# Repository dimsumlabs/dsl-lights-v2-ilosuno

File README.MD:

# dsl-light v2 (ilo suno)

This repo contains the electronic design files of the new revision of DSL's RGBW LED driver board.

The original one was designed by lionello. Since I don't have Eagle, I'm redrawing the whole thing. I made the following enhancements:

* Added white LED channel
* Using ESP-WROOM-02 instead of ESP12. Both are ESP8266-based chip.
* Added bypass capacitors
* Added reverse polarity protection for voltage regulator input
* Using SMD components except for connectors
* Added mounting holes
* Replaced LDO with DC-DC buck converter
* Added power indicator
* Added programming header and removed unneeded programming button
* Added GPIO header for potential future expansion
* Replaced first-stage BJT with MOSFET
* Added gate resistor to MOSFET
* Added Dimsumlabs' logo and other info on silk mark

This new hardware design is backward-compatible with the original firmware.

## Installation Progress in DSL

2024-08-14:

2024-10-29:

2025-09-13:

* Programmed the driver board with correct SSID and password so that it can be integrated with the lighting-related feature in DSL
* Obtained MAC and IP address of the driver boards so that the helios DNS can be fixed. The fix is to be performed by trouble
* Performed material recon for the installation of the backside

Thanks Nigel for wiring up the frontside driver board to the switch board. Also thanks Nigel for offering to help installing the LED strips to the backside.

2025-09-14:

* trouble had updated the DNS record. Now that the driver boards' web interface can be accessed via a domain name

2025-09-27:

* As Nigel's doing renovation, plan changed. The orignally installed strips had been rotated. Instead of using 2 LED controllers, we gotta use 5 of them. Sadale had put the 5 strips up but only one of them has controller installed for now.

2025-10-18:

* Ordered 10pcs additional units

2025-10-19:

* Drawn enclosure for the device

2025-11-01:

* Revised enclosure design with vents added
* Performed programming, flashing and testing on the 10pcs batch

2025-12-31:

* I haven't logged the progress but based on my visit in the past weeks, the installation has been completed (5 sets of LED controllers hanging on the ceiling). strerror had also vibe coded a web interface for controlling the lights!

## Credit

* lionello - For making the original design and the firmware
* Sadale - For revising the hardware design and doing the installation
* nigel - for reviewing the hardware design and doing the installation
* trouble - for proposing starting this project and reviewing the hardware design
* strerror - for doing the installation and making the web interface
* Other DSL members - for getting the whole thing installed to DSL, maintaining the firmware, etc.

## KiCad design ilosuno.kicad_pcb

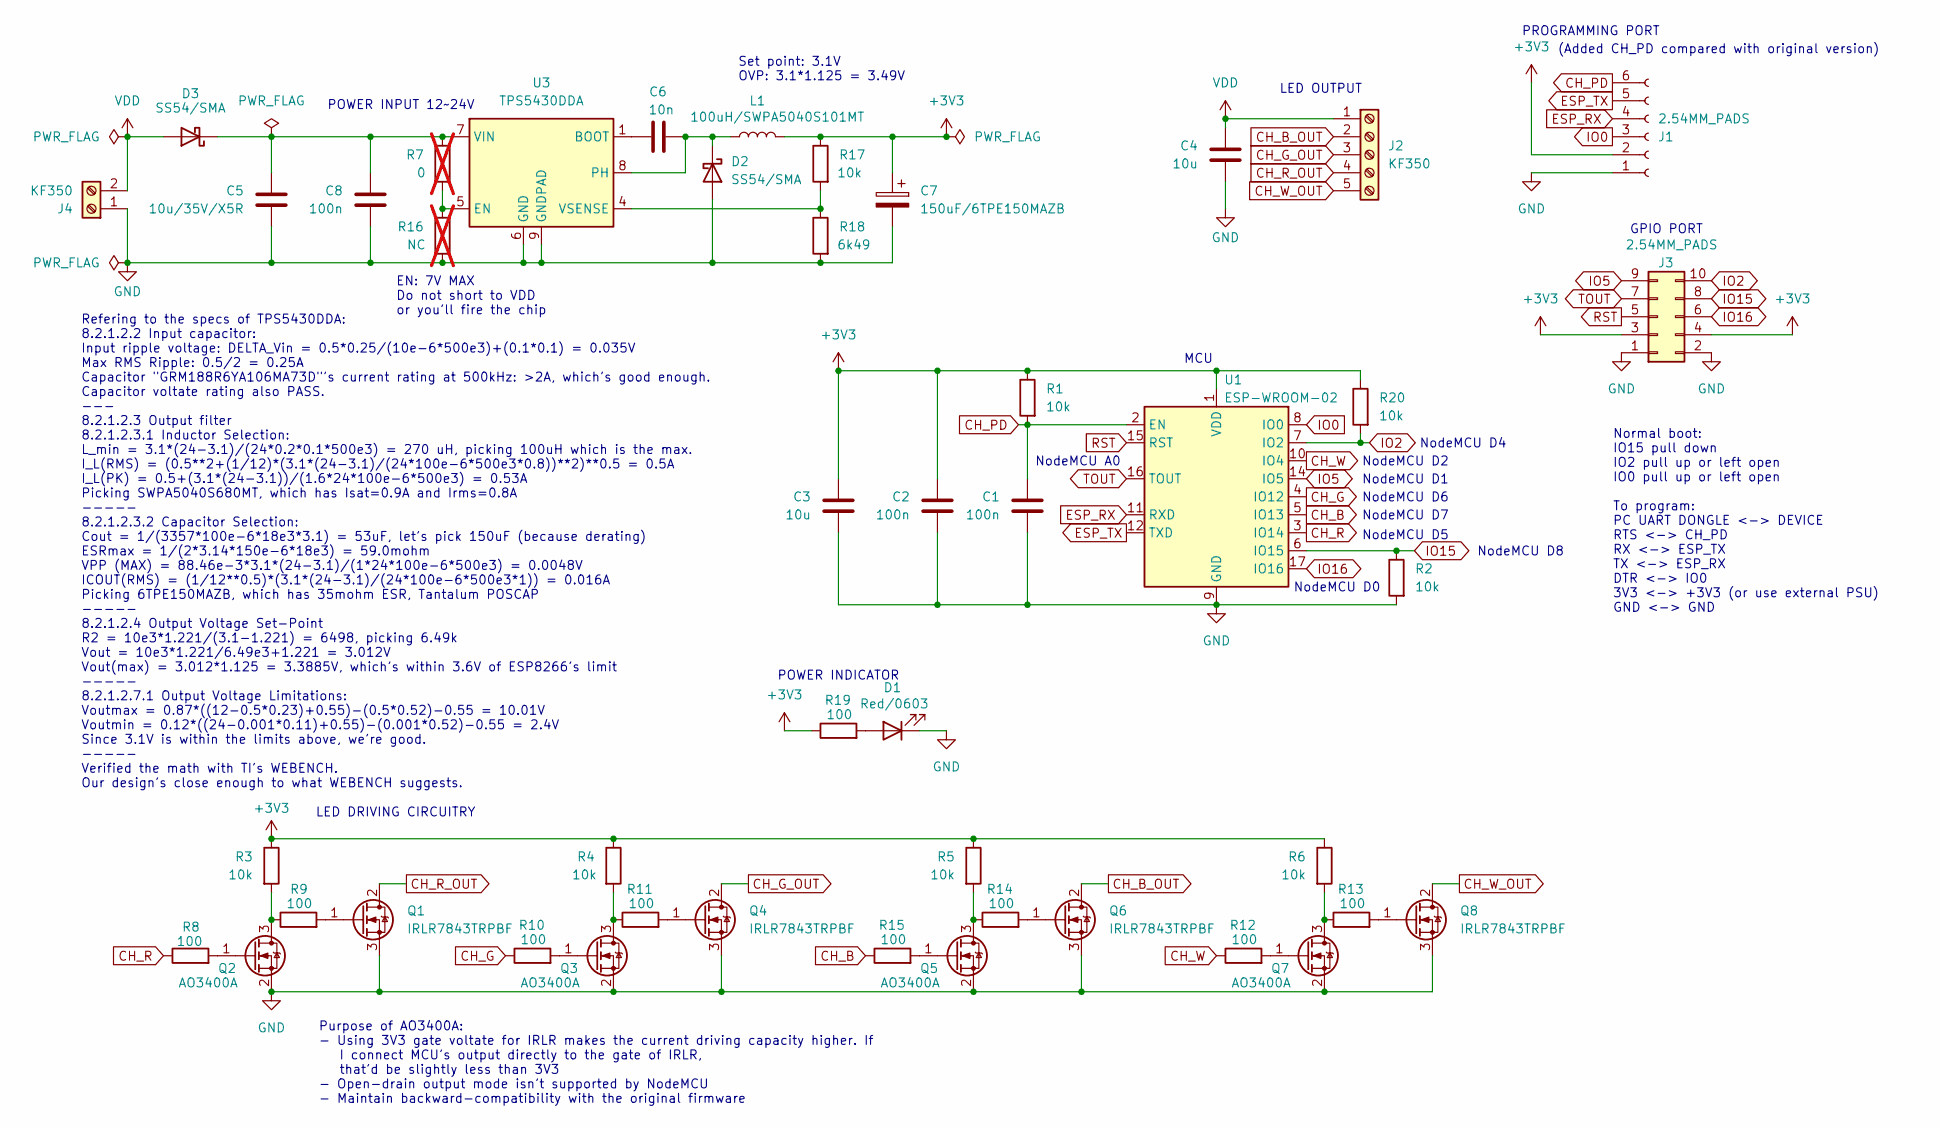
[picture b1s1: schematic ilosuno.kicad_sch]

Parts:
C1, C2, C8: 100n; C_0603_1608Metric; LCSC C14663
C3, C4: 10u; C_0805_2012Metric; LCSC C162422
C5: 10u/35V/X5R; C_0805_2012Metric; LCSC C162422
C6: 10n; C_0603_1608Metric; LCSC C57112
C7: 150uF/6TPE150MAZB; CP_EIA-3528-21_Kemet-B; LCSC C79110
D1: Red/0603; LED_0603_1608Metric; JLC Basic Part Y
D2, D3: SS54/SMA; D_SMA; LCSC C22452
J1: 2.54MM_PADS; PinHeader_1x06_P2.54mm_Vertical
J2: KF350; TerminalBlock_4Ucon_1x05_P3.50mm_Horizontal; LCSC both:C474893,C474892
J3: 2.54MM_PADS; PinHeader_2x05_P2.54mm_Vertical
J4: KF350; TerminalBlock_4Ucon_1x02_P3.50mm_Horizontal; LCSC C474892
L1: 100uH/SWPA5040S101MT; L_Sunlord_SWPA5040S; LCSC C88132
Q1, Q4, Q6, Q8: IRLR7843TRPBF; TO-252-2-with-heatsink; LCSC C21988
Q2, Q3, Q5, Q7: AO3400A; SOT-23; LCSC C20917
R1, R2, R3, R4, R5, R6, R17, R20: 10k; R_0603_1608Metric; LCSC C25804
R7: 0; R_0603_1608Metric; LCSC C21189; not fitted
R8, R9, R10, R11, R12, R13, R14, R15, R19: 100; R_0603_1608Metric; LCSC C22775
R16: NC; R_0603_1608Metric; not fitted
R18: 6k49; R_0603_1608Metric; LCSC C23088
U1: ESP-WROOM-02; LCSC C529584
U3: TPS5430DDA; TI_SO-PowerPAD-8_ThermalVias; LCSC C9864

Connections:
+3V3: C2.1, C3.1, C7.1, J1.2, J3.3, J3.4, L1.2, R1.1, R3.1, R4.1, R5.1, R6.1, R17.1, R19.1, R20.1, U1.1 (VDD)
CH_B: R15.1, U1.5 (IO13)
CH_B_OUT: J2.2, Q6.2 (D)
CH_G: R10.1, U1.4 (IO12)
CH_G_OUT: J2.3, Q4.2 (D)
CH_PD: C1.1, J1.6, R1.2, U1.2 (EN)
CH_R: R8.1, U1.3 (IO14)
CH_R_OUT: J2.4, Q1.2 (D)
CH_W: R12.1, U1.10 (IO4)
CH_W_OUT: J2.5, Q8.2 (D)
ESP_RX: J1.4, U1.11 (RXD)
ESP_TX: J1.5, U1.12 (TXD)
GND: C1.2, C2.2, C3.2, C4.2, C5.2, C7.2, C8.2, D1.1 (K), D2.2 (A), J1.1, J3.1, J3.2, J4.1, Q1.3 (S), Q2.2 (S), Q3.2 (S), Q4.3 (S), Q5.2 (S), Q6.3 (S), Q7.2 (S), Q8.3 (S), R2.2, R16.2, R18.2, U1.9 (GND), U1.13 (GND), U1.18 (GND), U1.19 (GND), U3.6 (GND), U3.9 (GNDPAD)
IO0: J1.3, U1.8 (IO0)
IO2: J3.10, R20.2, U1.7 (IO2)
IO5: J3.9, U1.14 (IO5)
IO15: J3.8, R2.1, U1.6 (IO15)
IO16: J3.6, U1.17 (IO16)
unnamed: D1.2 (A), R19.2
unnamed: C6.1, D2.1 (K), L1.1, U3.8 (PH)
unnamed: C5.1, C8.1, D3.1 (K), R7.1, U3.7 (VIN)
unnamed: Q1.1 (G), R9.2
unnamed: Q2.3 (D), R3.2, R9.1
unnamed: Q2.1 (G), R8.2
unnamed: Q3.3 (D), R4.2, R11.1
unnamed: Q3.1 (G), R10.2
unnamed: Q4.1 (G), R11.2
unnamed: Q5.3 (D), R5.2, R14.1
unnamed: Q5.1 (G), R15.2
unnamed: Q6.1 (G), R14.2
unnamed: Q7.3 (D), R6.2, R13.1
unnamed: Q7.1 (G), R12.2
unnamed: Q8.1 (G), R13.2
unnamed: C6.2, U3.1 (BOOT)
unnamed: R7.2, R16.1, U3.5 (EN)
unnamed: R17.2, R18.1, U3.4 (VSENSE)
RST: J3.5, U1.15 (RST)
TOUT: J3.7, U1.16 (TOUT)
VDD: C4.1, D3.2 (A), J2.1, J4.2

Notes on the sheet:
LED DRIVING CIRCUITRY
Set point: 3.1V OVP: 3.1*1.125 = 3.49V
(Added CH_PD compared with original version)
POWER INDICATOR
GPIO PORT
NodeMCU D5
LED OUTPUT
NodeMCU D4
Normal boot: IO15 pull down IO2 pull up or left open IO0 pull up or left open To program: PC UART DONGLE <-> DEVICE RTS <-> CH_PD RX <-> ESP_TX TX <-> ESP_RX DTR <-> IO0 3V3 <-> +3V3 (or use external PSU) GND <-> GND
NodeMCU D7
NodeMCU D2
MCU
PROGRAMMING PORT
NodeMCU D6
Purpose of AO3400A: - Using 3V3 gate voltate for IRLR makes the current driving capacity higher. If I connect MCU's output directly to the gate of IRLR, that'd be slightly less than 3V3 - Open-drain output mode isn't supported by NodeMCU - Maintain backward-compatibility with the original firmware
Refering to the specs of TPS5430DDA: 8.2.1.2.2 Input capacitor: Input ripple voltage: DELTA_Vin = 0.5*0.25/(10e-6*500e3)+(0.1*0.1) = 0.035V Max RMS Ripple: 0.5/2 = 0.25A Capacitor "GRM188R6YA106MA73D"'s current rating at 500kHz: >2A, which's good enough. Capacitor voltate rating also PASS. --- 8.2.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
EN: 7V MAX Do not short to VDD or you'll fire the chip
NodeMCU D0
POWER INPUT 12~24V
NodeMCU D1
NodeMCU D8
NodeMCU A0

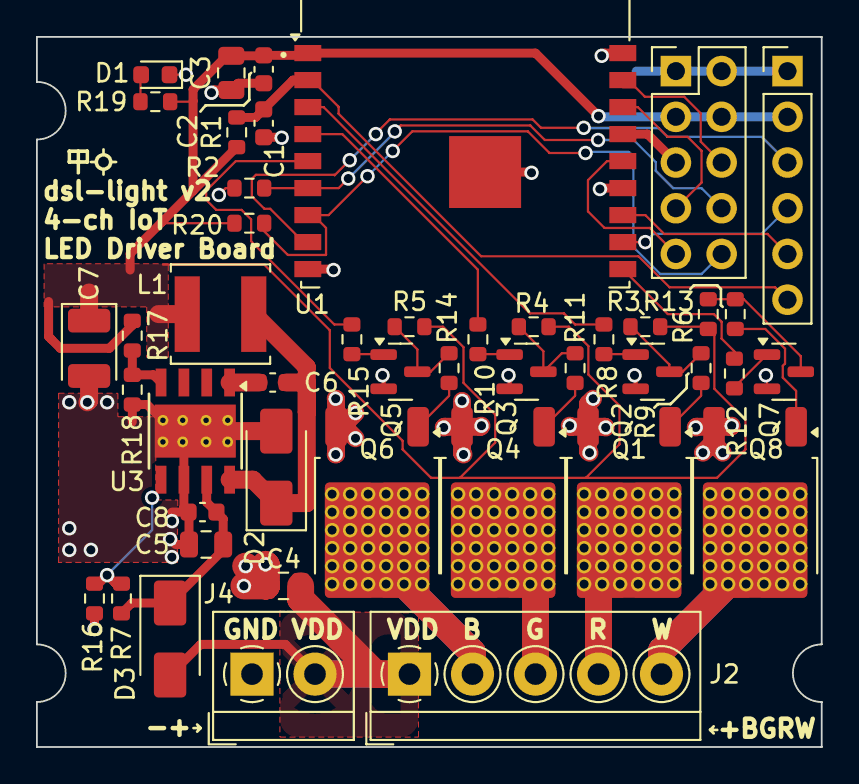
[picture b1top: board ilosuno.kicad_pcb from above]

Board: 2 copper layers, 43.6 x 39.5 mm, 46 parts (0 on the bottom side), 39 nets.

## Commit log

2024-07-27 Initial commit - revision 0g
2024-07-28 rev1a: Fixed buck converter output overvoltage bug. Added reverse polarity protection. Exposed more pins to GPIO header (RST, IO2 and IO15)
2024-08-03 rev1b: Corrected silk mark in regard to the required initial boot pin state, with on-board pull-down considered
2024-08-03 Documented the math for buck converter with the new capacitor value, inductor value and the new voltage set point
2024-08-10 Bug fixed: Buck converter EN pin overvoltage
2024-10-17 Added pic descripting the installation progress in DSL
2024-10-30 Documented the installation progress as of 2024-10-29
2025-09-13 Documented the installation progress as of 2025-09-13
2025-09-14 DNS updated by trouble
2025-10-19 Added first revision of enclosure
2025-10-19 Updated README for the latest progress
2025-10-19 Added LED indicator hole on the enclosure
2025-11-01 enclosure: Added vents; Enlarged clearance hole to 2.9mm
2025-11-01 Documented latest progress
2025-11-02 enclosure: Increased LED indicator hole size from 1mm to 2mm
2025-11-05 enclosure: Enlarged the tapping hole size from 2mm to 2.1mm to account for 3D printing shrinkage
2025-12-31 Updated with info on the latest project status
